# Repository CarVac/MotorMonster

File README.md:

# MotorMonster

MotorMonster is intended to be a 5x TMC2160 stepper driver board for 3D printers and other applications, that is actually designed to properly drive the optimal currents for high performance NEMA 17 motors: just north of 2.8 amps RMS.

Many existing 3D printer boards use improper sense resistors.
The BTT SKR Pico, for example, has a limit of 1.4 amps RMS due to its high sense resistor values.
Conversely, the BTT Kraken overspecs its currents with extremely low sense resistors, leaving the TMC drivers starved for sense voltage resolution.

Other boards use StepStick drivers for modularity, but those have worse thermal dissipation than integrated drivers.

The goal of this project is to have a focused, single-board solution for high performance motor driving, leaving everything else to be left to a standard 3D printer motherboard.
With 5 drivers, it should be suitable for 4WD CoreXY + an extruder, or cross gantry + an extruder.

You can choose what sense resistors you want to tailor the board to your own needs.

The MCU is an RP2040, which may be a tad bit slow for the very fastest applications but it's a chip I have a lot of experience with, reducing development risk.

# Acknowledgements

The RP2040 and supporting circuitry is based on https://github.com/Armastardo/OpenRectangleTemplate

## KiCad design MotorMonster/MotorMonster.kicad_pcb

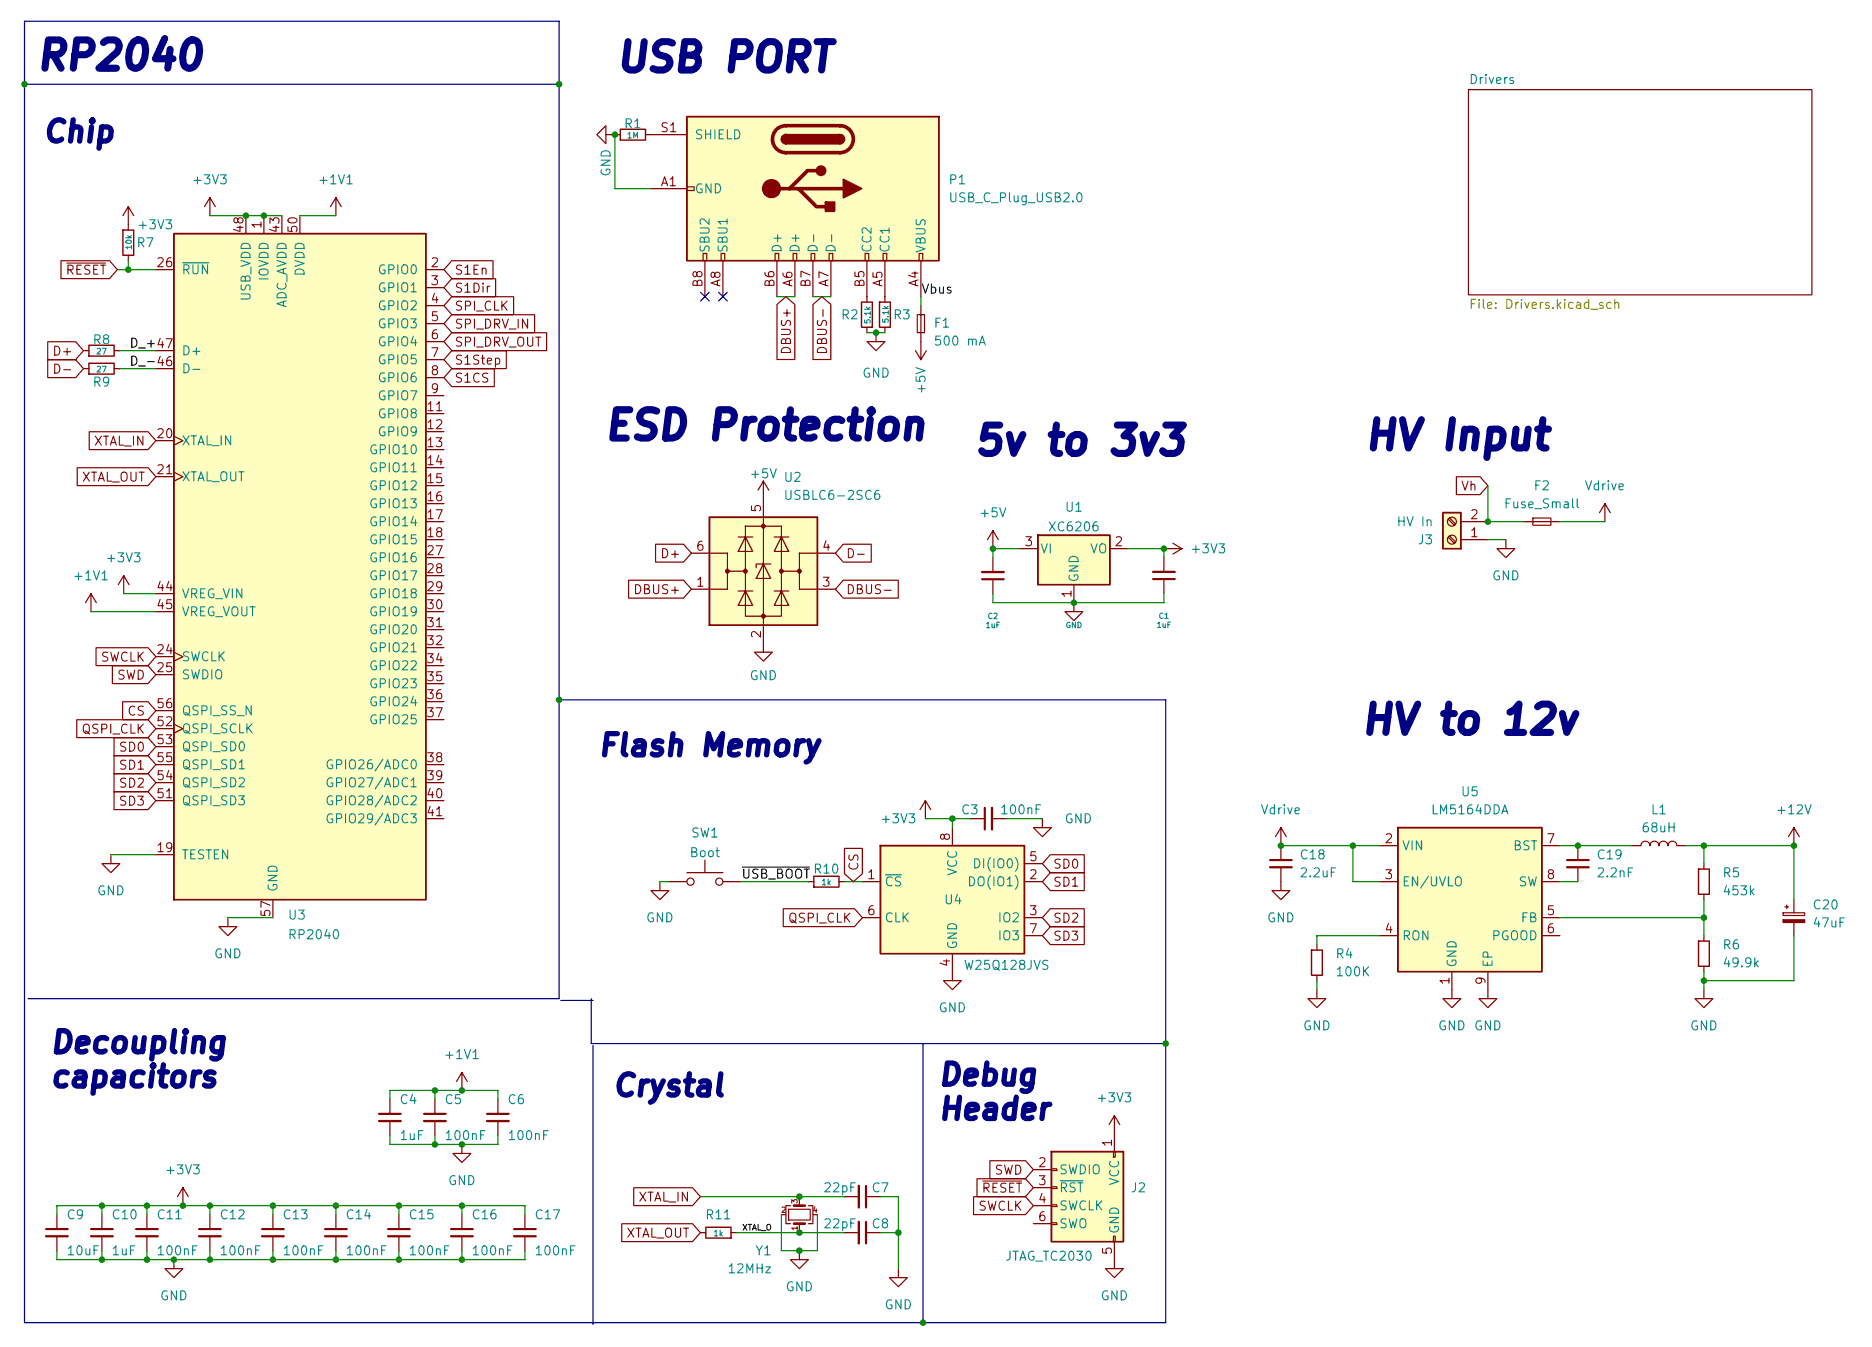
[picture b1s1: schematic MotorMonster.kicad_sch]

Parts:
C1, C2, C4, C10: 1uF; C_0402_1005Metric; LCSC C52923
C3, C5, C6, C11, C12, C13, C14, C15, C16, C17: 100nF; C_0402_1005Metric; LCSC C1525
C7, C8: 22pF; C_0402_1005Metric; LCSC C1555
C9: 10uF; C_0402_1005Metric; LCSC C15525
C18: 2.2uF; C_1206_3216Metric_Pad1.33x1.80mm_HandSolder; LCSC C170101
C19: 2.2nF; C_0603_1608Metric_Pad1.08x0.95mm_HandSolder; LCSC C113804
C20: 47uF; C_1206_3216Metric_Pad1.33x1.80mm_HandSolder; LCSC C403725
F1: 500 mA; Fuse_1206_3216Metric; LCSC C70076
F2: Fuse_Small; Fuseholder_Clip-6.3x32mm_Littelfuse_122_Inline_P34.21x7.62m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
J2: JTAG_TC2030; CON_TC2030_outlined
J3: HV In; TerminalBlock_Altech_AK300-2_P5.00mm
L1: 68uH; L_12x12mm_H8mm; LCSC C2929504
P1: USB_C_Plug_USB2.0; USB_C_Receptacle_G-Switch_GT-USB-7010ASV; LCSC C2988369
R1: 1M; R_0603_1608Metric; LCSC C22935
R2, R3: 5.1k; R_0402_1005Metric; LCSC C25905
R4: 100K; R_0402_1005Metric_Pad0.72x0.64mm_HandSolder; LCSC C217682
R5: 453k; R_0402_1005Metric_Pad0.72x0.64mm_HandSolder; LCSC C27009
R6: 49.9k; R_0402_1005Metric_Pad0.72x0.64mm_HandSolder; LCSC C25897
R7: 10k; R_0402_1005Metric; LCSC C25744
R8, R9: 27; R_0603_1608Metric; LCSC C25190
R10, R11: 1k; R_0402_1005Metric; LCSC C11702
SW1: Boot; SW_SPST_SKQG_WithStem; LCSC C318884
U1: XC6206; SOT-23; LCSC C5446
U2: USBLC6-2SC6; SOT-23-6; LCSC C7519
U3: RP2040; RP2040-QFN-56; LCSC C2040
U4: W25Q128JVS; SOIC-8_5.23x5.23mm_P1.27mm; LCSC C97521
U5: LM5164DDA; HSOP-8-1EP_3.9x4.9mm_P1.27mm_EP2.41x3.1mm_ThermalVias; LCSC C477928
Y1: 12MHz; Crystal_SMD_3225-4Pin_3.2x2.5mm; LCSC C9002

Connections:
+1V1: C4.1, C5.1, C6.1, U3.23 (DVDD), U3.45 (VREG_VOUT), U3.50 (DVDD)
+3V3: C1.2, C3.1, C9.1, C10.1, C11.1, C12.1, C13.1, C14.1, C15.1, C16.1, C17.1, J2.1 (VCC), R7.1, U1.2 (VO), U3.1 (IOVDD), U3.10 (IOVDD), U3.22 (IOVDD), U3.33 (IOVDD), U3.42 (IOVDD), U3.43 (ADC_AVDD), U3.44 (VREG_VIN), U3.48 (USB_VDD), U3.49 (IOVDD), U4.8 (VCC); also elsewhere on the board
+5V: C2.2, F1.2, U1.3 (VI), U2.5 (VBUS)
+12V: C20.1, L1.2, R5.1; also elsewhere on the board
/D_+: R8.2, U3.47 (D+)
/D_-: R9.2, U3.46 (D-)
/Vbus: F1.1, P1.A4 (VBUS), P1.A9 (VBUS), P1.B4 (VBUS), P1.B9 (VBUS)
/XTAL_O: C8.2, R11.1, Y1.1
/~USB_BOOT: R10.1, SW1.2
CS: R10.2, U3.56 (QSPI_SS_N), U4.1 (~CS)
D+: R8.1, U2.6 (I/O1)
D-: R9.1, U2.4 (I/O2)
DBUS+: P1.A6 (D+), P1.B6 (D+), U2.1 (I/O1)
DBUS-: P1.A7 (D-), P1.B7 (D-), U2.3 (I/O2)
GND: C1.1, C2.1, C3.2, C4.2, C5.2, C6.2, C7.1, C8.1, C9.2, C10.2, C11.2, C12.2, C13.2, C14.2, C15.2, C16.2, C17.2, C18.2, C20.2, J2.5 (GND), J3.1, P1.A1 (GND), P1.A12 (GND), P1.B1 (GND), P1.B12 (GND), R1.1, R2.1, R3.2, R4.2, R6.2, SW1.1, U1.1 (GND), U2.2 (GND), U3.19 (TESTEN), U3.57 (GND), U4.4 (GND), U5.1 (GND), U5.9 (EP), Y1.2, Y1.4; also elsewhere on the board
unnamed: P1.A5 (CC1), R3.1
unnamed: P1.B5 (CC2), R2.2
unnamed: P1.S1 (SHIELD), R1.2
unnamed: C19.1, L1.1, U5.7 (BST)
unnamed: R5.2, R6.1, U5.5 (FB)
unnamed: R4.1, U5.4 (RON)
unnamed: C19.2, U5.8 (SW)
QSPI_CLK: U3.52 (QSPI_SCLK), U4.6 (CLK)
S1CS: U3.8 (GPIO6); also elsewhere on the board
S1Dir: U3.3 (GPIO1); also elsewhere on the board
S1En: U3.2 (GPIO0); also elsewhere on the board
S1Step: U3.7 (GPIO5); also elsewhere on the board
SD0: U3.53 (QSPI_SD0), U4.5 (DI(IO0))
SD1: U3.55 (QSPI_SD1), U4.2 (DO(IO1))
SD2: U3.54 (QSPI_SD2), U4.3 (IO2)
SD3: U3.51 (QSPI_SD3), U4.7 (IO3)
SPI_CLK: U3.4 (GPIO2); also elsewhere on the board
SPI_DRV_IN: U3.5 (GPIO3); also elsewhere on the board
SPI_DRV_OUT: U3.6 (GPIO4); also elsewhere on the board
SWCLK: J2.4 (SWCLK), U3.24 (SWCLK)
SWD: J2.2 (SWDIO), U3.25 (SWDIO)
Vdrive: C18.1, F2.2, U5.2 (VIN), U5.3 (EN/UVLO); also elsewhere on the board
Vh: F2.1, J3.2
XTAL_IN: C7.2, U3.20 (XTAL_IN), Y1.3
XTAL_OUT: R11.2, U3.21 (XTAL_OUT)
~RESET: J2.3 (~RST), R7.2, U3.26 (~RUN)

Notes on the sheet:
Crystal
USB PORT
HV Input
Flash Memory
HV to 12v
RP2040
Debug Header
Chip
5v to 3v3
ESD Protection
Decoupling capacitors

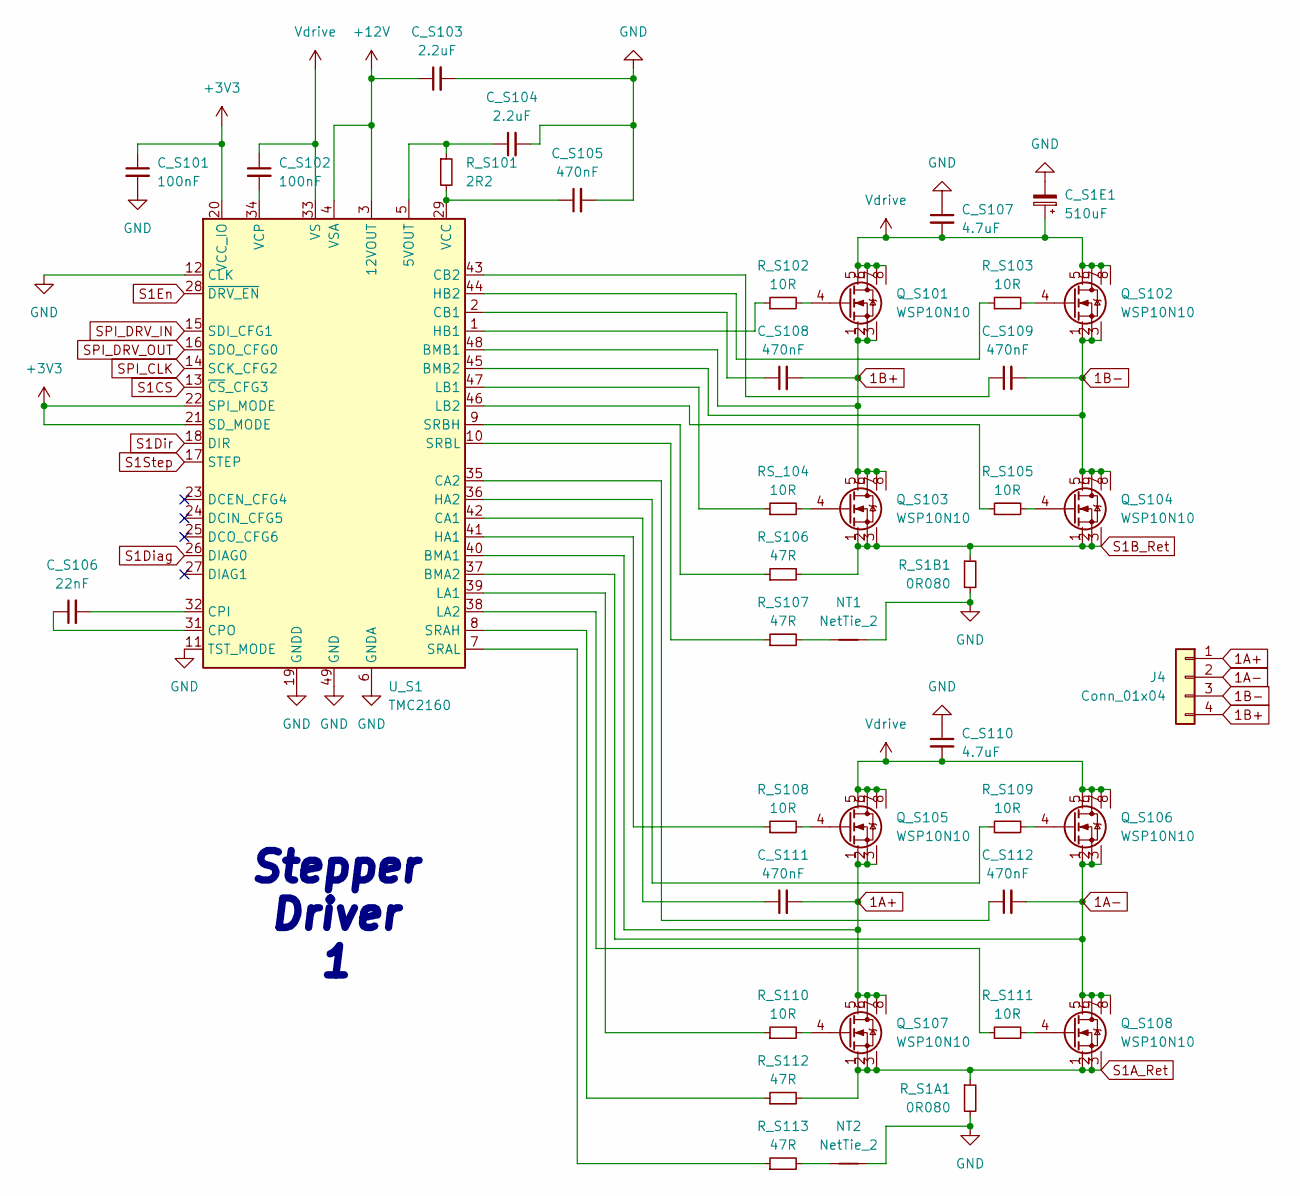
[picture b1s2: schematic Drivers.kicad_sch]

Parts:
C_S1E1: 510uF; CP_Radial_D18.0mm_P7.50mm
C_S101: 100nF; C_0402_1005Metric_Pad0.74x0.62mm_HandSolder; LCSC C1525
C_S102: 100nF; C_0402_1005Metric_Pad0.74x0.62mm_HandSolder; LCSC C162178
C_S103, C_S104: 2.2uF; C_0603_1608Metric_Pad1.08x0.95mm_HandSolder; LCSC C57895
C_S105, C_S108, C_S109, C_S111, C_S112: 470nF; C_1206_3216Metric_Pad1.33x1.80mm_HandSolder; LCSC C313105
C_S106: 22nF; C_0603_1608Metric_Pad1.08x0.95mm_HandSolder; LCSC C313105
C_S107, C_S110: 4.7uF; C_1210_3225Metric_Pad1.33x2.70mm_HandSolder; LCSC C2979983
J4: Conn_01x04; JST_XH_B4B-XH-A_1x04_P2.50mm_Vertical
NT1, NT2: NetTie_2; NetTie-2_SMD_Pad0.5mm
Q_S101, Q_S102, Q_S103, Q_S104, Q_S105, Q_S106, Q_S107, Q_S108: WSP10N10; SOIC-8_3.9x4.9mm_P1.27mm; LCSC C2827250
RS_104: 10R; R_0402_1005Metric_Pad0.72x0.64mm_HandSolder; LCSC C284283
R_S1A1, R_S1B1: 0R080; R_2512_6332Metric_Pad1.40x3.35mm_HandSolder; LCSC C5154744
R_S101: 2R2; R_0603_1608Metric_Pad0.98x0.95mm_HandSolder; LCSC C861308
R_S102, R_S103, R_S105, R_S108, R_S109, R_S110, R_S111: 10R; R_0402_1005Metric_Pad0.72x0.64mm_HandSolder; LCSC C284283
R_S106, R_S107, R_S112, R_S113: 47R; R_0402_1005Metric_Pad0.72x0.64mm_HandSolder; LCSC C284589
U_S1: TMC2160; TQFP-48-1EP_7x7mm_P0.5mm_EP5x5mm; LCSC C465948

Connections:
1A+: C_S111.2, J4.1, Q_S105.1 (D), Q_S105.2 (G), Q_S105.3 (S), Q_S107.5, Q_S107.6, Q_S107.7, Q_S107.8, U_S1.40 (BMA1)
1A-: C_S112.2, J4.2, Q_S106.1 (D), Q_S106.2 (G), Q_S106.3 (S), Q_S108.5, Q_S108.6, Q_S108.7, Q_S108.8, U_S1.37 (BMA2)
1B+: C_S108.2, J4.4, Q_S101.1 (D), Q_S101.2 (G), Q_S101.3 (S), Q_S103.5, Q_S103.6, Q_S103.7, Q_S103.8, U_S1.48 (BMB1)
1B-: C_S109.2, J4.3, Q_S102.1 (D), Q_S102.2 (G), Q_S102.3 (S), Q_S104.5, Q_S104.6, Q_S104.7, Q_S104.8, U_S1.45 (BMB2)
+3V3: C_S101.1, U_S1.20 (VCC_IO), U_S1.21 (SD_MODE), U_S1.22 (SPI_MODE); also elsewhere on the board
+12V: C_S103.1, U_S1.3 (12VOUT), U_S1.4 (VSA); also elsewhere on the board
GND: C_S1E1.2, C_S101.2, C_S103.2, C_S104.2, C_S105.2, C_S107.1, C_S110.1, NT1.2, NT2.2, R_S1A1.2, R_S1B1.2, U_S1.6 (GNDA), U_S1.11 (TST_MODE), U_S1.12 (CLK), U_S1.19 (GNDD), U_S1.30 (GNDD), U_S1.49 (GND); also elsewhere on the board
unnamed: NT1.1, R_S107.2
unnamed: NT2.1, R_S113.2
unnamed: Q_S101.4, R_S102.2
unnamed: Q_S102.4, R_S103.2
unnamed: Q_S103.4, RS_104.2
unnamed: Q_S104.4, R_S105.2
unnamed: Q_S105.4, R_S108.2
unnamed: Q_S106.4, R_S109.2
unnamed: Q_S107.4, R_S110.2
unnamed: Q_S108.4, R_S111.2
unnamed: C_S104.1, R_S101.1, U_S1.5 (5VOUT)
unnamed: C_S111.1, U_S1.42 (CA1)
unnamed: C_S112.1, U_S1.35 (CA2)
unnamed: C_S108.1, U_S1.2 (CB1)
unnamed: C_S109.1, U_S1.43 (CB2)
unnamed: C_S106.2, U_S1.32 (CPI)
unnamed: C_S106.1, U_S1.31 (CPO)
unnamed: R_S108.1, U_S1.41 (HA1)
unnamed: R_S109.1, U_S1.36 (HA2)
unnamed: R_S102.1, U_S1.1 (HB1)
unnamed: R_S103.1, U_S1.44 (HB2)
unnamed: R_S110.1, U_S1.39 (LA1)
unnamed: R_S111.1, U_S1.38 (LA2)
unnamed: RS_104.1, U_S1.47 (LB1)
unnamed: R_S105.1, U_S1.46 (LB2)
unnamed: R_S112.1, U_S1.8 (SRAH)
unnamed: R_S113.1, U_S1.7 (SRAL)
unnamed: R_S106.1, U_S1.9 (SRBH)
unnamed: R_S107.1, U_S1.10 (SRBL)
unnamed: C_S105.1, R_S101.2, U_S1.29 (VCC)
unnamed: C_S102.2, U_S1.34 (VCP)
S1A_Ret: Q_S107.1 (D), Q_S107.2 (G), Q_S107.3 (S), Q_S108.1 (D), Q_S108.2 (G), Q_S108.3 (S), R_S1A1.1, R_S112.2
S1B_Ret: Q_S103.1 (D), Q_S103.2 (G), Q_S103.3 (S), Q_S104.1 (D), Q_S104.2 (G), Q_S104.3 (S), R_S1B1.1, R_S106.2
S1CS: U_S1.13 (~CS_CFG3); also elsewhere on the board
S1Diag: U_S1.26 (DIAG0)
S1Dir: U_S1.18 (DIR); also elsewhere on the board
S1En: U_S1.28 (~DRV_EN); also elsewhere on the board
S1Step: U_S1.17 (STEP); also elsewhere on the board
SPI_CLK: U_S1.14 (SCK_CFG2); also elsewhere on the board
SPI_DRV_IN: U_S1.15 (SDI_CFG1); also elsewhere on the board
SPI_DRV_OUT: U_S1.16 (SDO_CFG0); also elsewhere on the board
Vdrive: C_S1E1.1, C_S102.1, C_S107.2, C_S110.2, Q_S101.5, Q_S101.6, Q_S101.7, Q_S101.8, Q_S102.5, Q_S102.6, Q_S102.7, Q_S102.8, Q_S105.5, Q_S105.6, Q_S105.7, Q_S105.8, Q_S106.5, Q_S106.6, Q_S106.7, Q_S106.8, U_S1.33 (VS); also elsewhere on the board

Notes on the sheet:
Stepper Driver 1

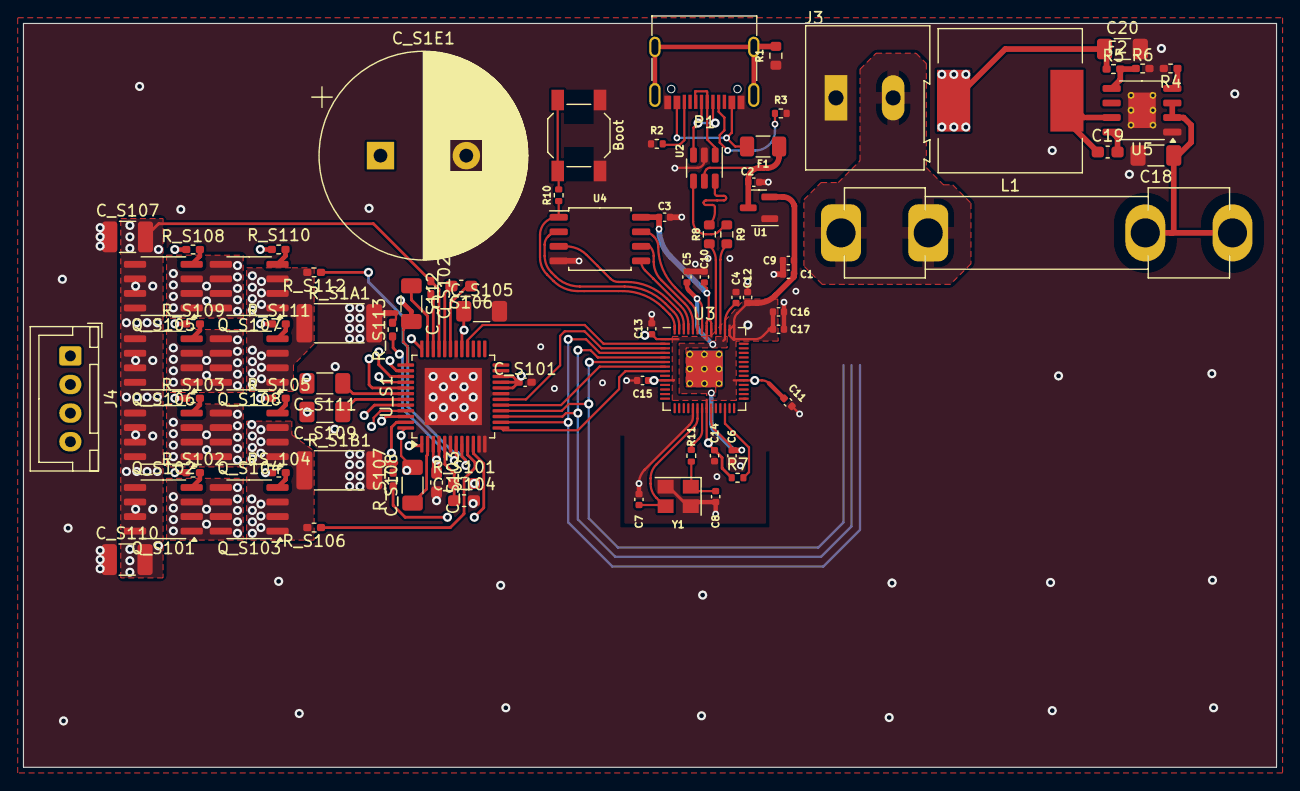
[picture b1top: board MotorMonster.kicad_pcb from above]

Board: 4 copper layers, 109.5 x 65.0 mm, 83 parts (0 on the bottom side), 76 nets.

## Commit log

2024-07-30 mention that the sense resistors can be changed
2024-07-31 basic layout and some routing done
2024-08-02 fully laid out
